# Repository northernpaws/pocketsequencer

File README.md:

# Pocket Sequencer

> This sequencer is being revised in revision 2 as a target for my embedded Rust audio processing framework, Rythm. Revision 2 will be a carrier board for one of the Rythm modules, and use the Rythm engine for the audio and sequencing.
>
> [https://github.com/northernpaws/rythm](https://github.com/northernpaws/rythm)

|  |  |
|:---:|:---:|

[Board Schematic](https://kicanvas.org/?github=https%3A%2F%2Fgithub.com%2Fnorthernpaws%2Fpocketsequencer%2Fblob%2Fmain%2Fhardware%2Fboards%2Fv0.1%2Fpocket_synth.kicad_pro)

[Board v0.1 Errata](hardware/boards/v0.1/README.md)

This repository contains my project for an STM32H7-based sequencer, synthesizer, and sampler, all in a small phone-sized pocketable form factor. 

  * 480 MHz Arm® Cortex®-M7 32-bit Processor (`STM32H743ZIT6`)
    * Floating-point unit
    * DSP instructions
    * High-speed memory controller
    * Quad SPI interface for flash
    * High-speed USB host and device mode
    * Several SAI audio blocks
  * 2.8" 240x320 TFT IPS Display (`ER-TFT028A2-4`)
  * 24 bit Audio Codec (`NAU88C22YG`)
    * DAC: 94dB SNR
    * ADC: 90dB SNR
    * 1W 8Ω BTL speaker driver
    * 40mW 16Ω headphone driver
  * Optional Bluetooth and Wifi (`nRF5430`)
    * Wirelessly connect Bluethooth headphones and speakers
    * Supports various high-fedality audio protocols
    * BLE MIDI
    * Wifi sample management and transfer
  * Interal stereo 8W speakers speaker
  * Internal MEMs microphone
  * SDRAM for sample pool and audio processing
    * Part allocated to in-memory sample pool for project
    * Part allocated to audio effects processing
    * Variable sizes in similar footprint available, up to 512Mbit:
        * 16bit * 48000Hz = 768,000b/s = 0.768Mb/s
        * 128Mb / 0.768Mb/s = 166.66 seconds of mono audio (`IS42S16800J-7TL`)
        * 256Mb / 0.768Mb/s = 333.33 seconds of mono audio (`IS42S16160J-7TLI`)
        * 512Mb / 0.768Mb/s = 666.66 seconds of mono audio (`IS42S16320F-7TLI`)
  * Micro SD Card
    * Saving and loading projects
      * Transfer and back up projects to a computer
    * Saving and loading samples
      * Load samples from a computer
      * Save samples recorded on the device
  * 3.3v NOR Flash (`MT25QUxxxxxx1xW7` 256M/128M/64M)
    * Stores device settings
    * Small storage space for projects and samples without SD card
    * Provides storage for cross-SD card samples
  * USB-C
    * USB-PD fast charging
    * Possible future audio interface mode
    * USB MIDI in and out
  * MIDI in/out via TRS minijack type A
  * 16 Multi-Purpose primary keys
    * Hot-swappable Kalih V1 Choc keyswitches
    * Addressable RGB LEDs for state indicators
  * Accelerometer and Gyroscope (`LSM6DS3`)
    * Can be used as sequencer parameters
    * Can be recorded for automation inputs

## Step Sequencer

The step sequencer on the device is modeled after popular semantics used by hardware sequencers, such as the Elektron Digitone and Digitakt, OP-1, OP-Z, Pocket Operators, Woovebox, etc.

> The hard requirements of the step sequencer and audio engine are not defined yet because they are under active development.

  * As many projects as the SD card or internal memory can store
    * 128 Patterns (TBD)
      * 8-16 Audio or MIDI tracks per pattern (TBD)
    * 8-24 Songs (arrangements of patterns) (TBD)
  * 8-16 voice polyphony (TBD)
    * 2-3 LFO per voice (TBD)

## Audio Samples

The primary audio engine runs in 32-bit and supports stereo audio.

### Sampling

The sampling engine runs 16bit 44.1Khz and saves and loads samples in single-channel mono.

Samples recoded from the internal or external mic are sampled at 24 bits into the device's SDRAM to provide a decent noise floor, and then filtered and downsampled to 16 bits for saving after they've been edited by the user.

The 16bit @ 44.1Khz sampling parameters provdes a good balance between audio quality, and reasonable utilization of the SDRAM without needing extremely large and expensive SDRAM chips:

```
16bit * 48000Hz = 768,000b/s = 0.768Mb/s
128Mb / 0.768Mb/s = 166.66 seconds of mono audio
256Mb / 0.768Mb/s = 333.33 seconds of mono audio
512Mb / 0.768Mb/s = 666.66 seconds of mono audio
```

> Note that some of the space calculated above (actual amount will be configurable) is allocated to the audio effects processing chain, i.e. for reverb and delay. 

## References

### Debugging

 - HardFault: Under XPERIPHERALS in Cortex-debug check the `CFSR_UFSR_BFSR_MMFSR` register to see the fault code and reference: https://community.st.com/t5/stm32-mcus/how-to-debug-a-hardfault-on-an-arm-cortex-m-stm32/ta-p/672235#toc-hId--1471762501

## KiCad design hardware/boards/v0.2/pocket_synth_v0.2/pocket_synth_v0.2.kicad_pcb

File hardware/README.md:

# Hardware

## Components

  * [480 MHz Arm® Cortex®-M7 32-bit Processor (`STM32H743ZIT6`)](https://www.st.com/en/microcontrollers-microprocessors/stm32h743zi.html)
    * Floating-point unit
    * DSP instructions
    * High-speed memory controller
    * Quad SPI interface for flash
    * High-speed USB host and device mode
    * Several SAI audio blocks
  * [24 bit Audio Codec (`NAU88C22YG`)](https://www.nuvoton.com/products/smart-home-audio/audio-converters/audio-codec-series/nau88c22yg/)
    * DAC: 94dB SNR and -84dB THD (“A” weighted)
    * ADC: 90dB SNR and -80dB THD (“A” weighted)
    * Integrated BTL speaker driver: 1W into 8Ω
    * Integrated head-phone driver: 40mW into 16Ω
  * [Optional Bluetooth Audio & MIDI (`nRF5340`)](https://www.nordicsemi.com/Products/nRF5340)
    * Wirelessly connect Bluethooth headphones and speakers
    * Connect devices for BLE MIDI inputs and outputs
    * uFL connector for case-mounted antenna
  * [Optional Wi-Fi (`ESP32-S2-MINI-2U`)](https://www.espressif.com/sites/default/files/documentation/esp32-s2-mini-2_esp32-s2-mini-2u_datasheet_en.pdf)
    * Wi-Fi sample management and transfer
    * uFL connector for case-mounted antenna

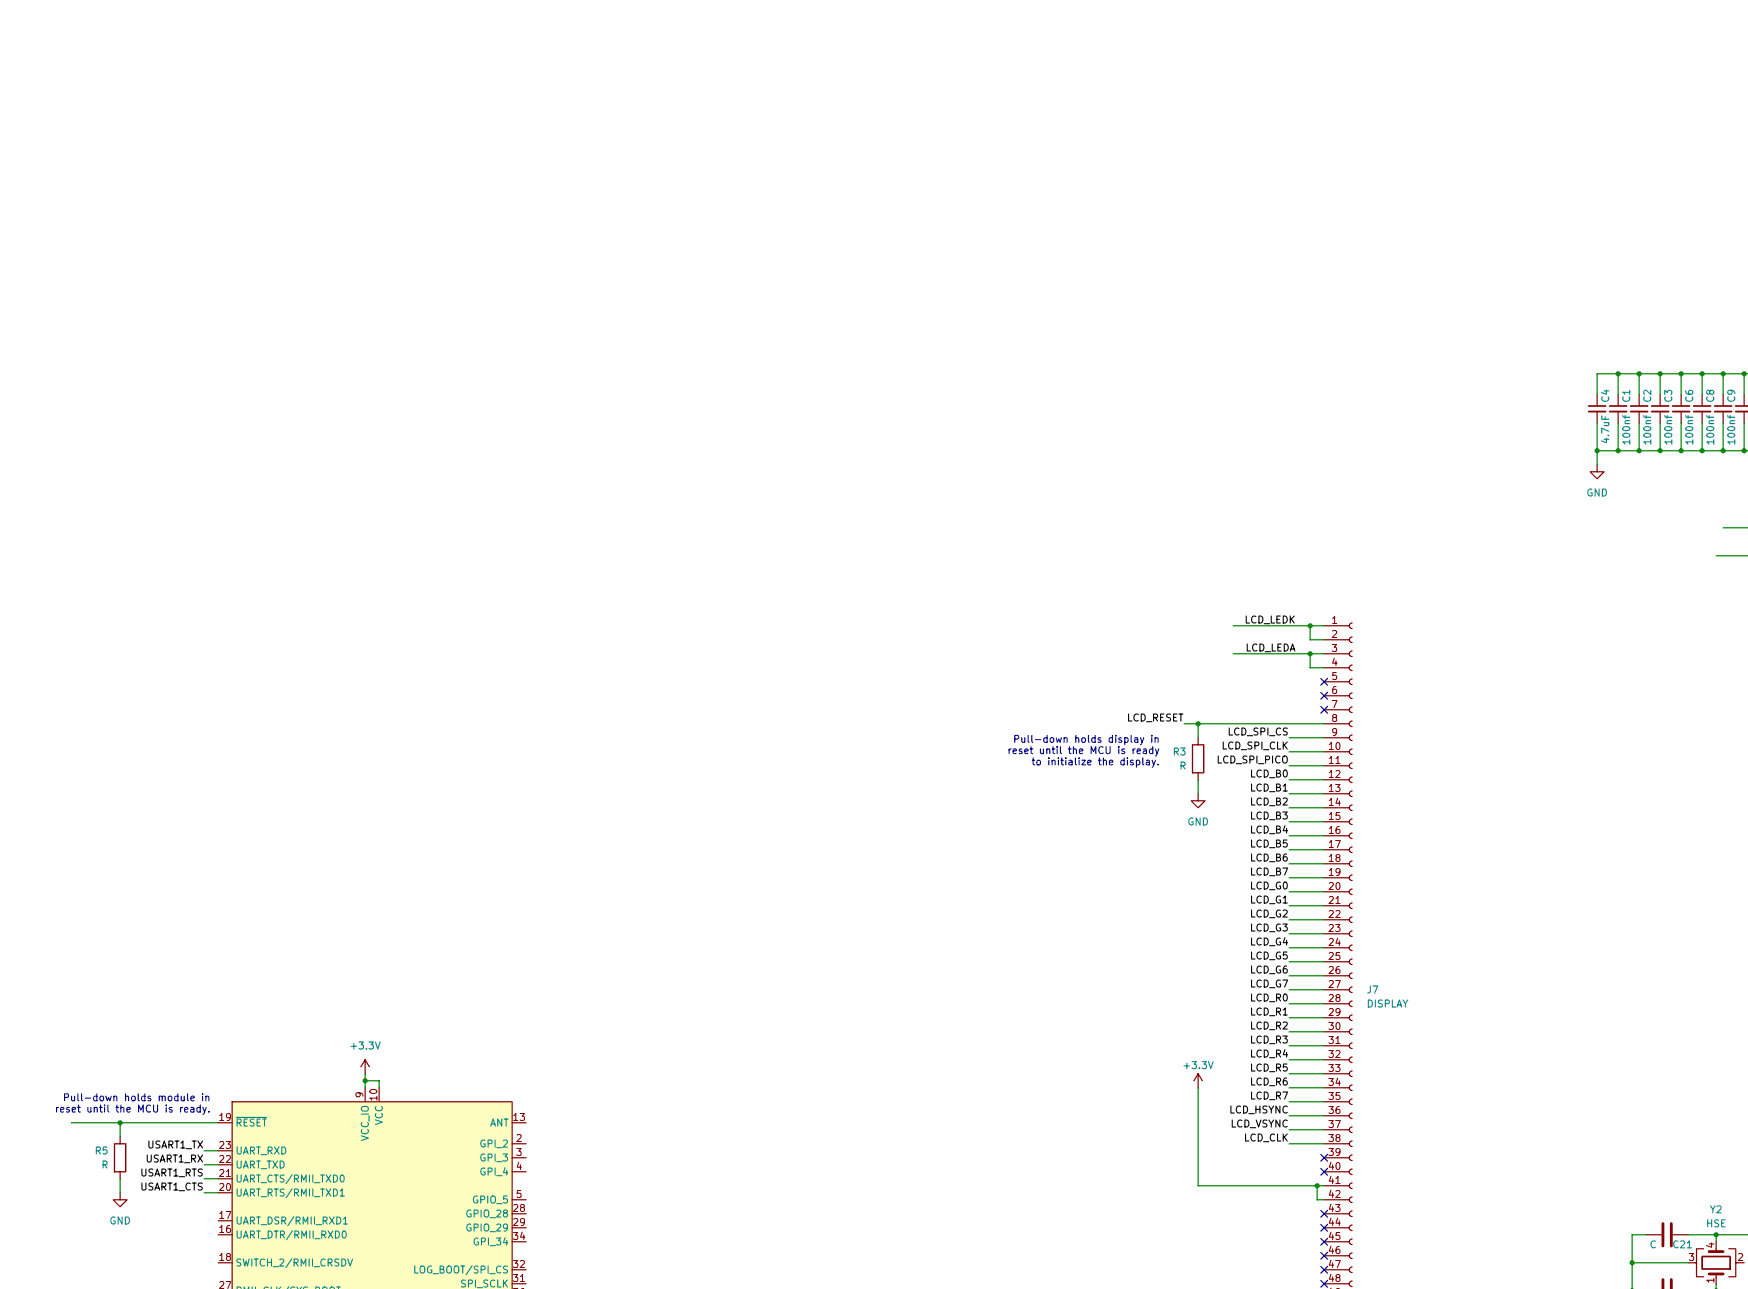
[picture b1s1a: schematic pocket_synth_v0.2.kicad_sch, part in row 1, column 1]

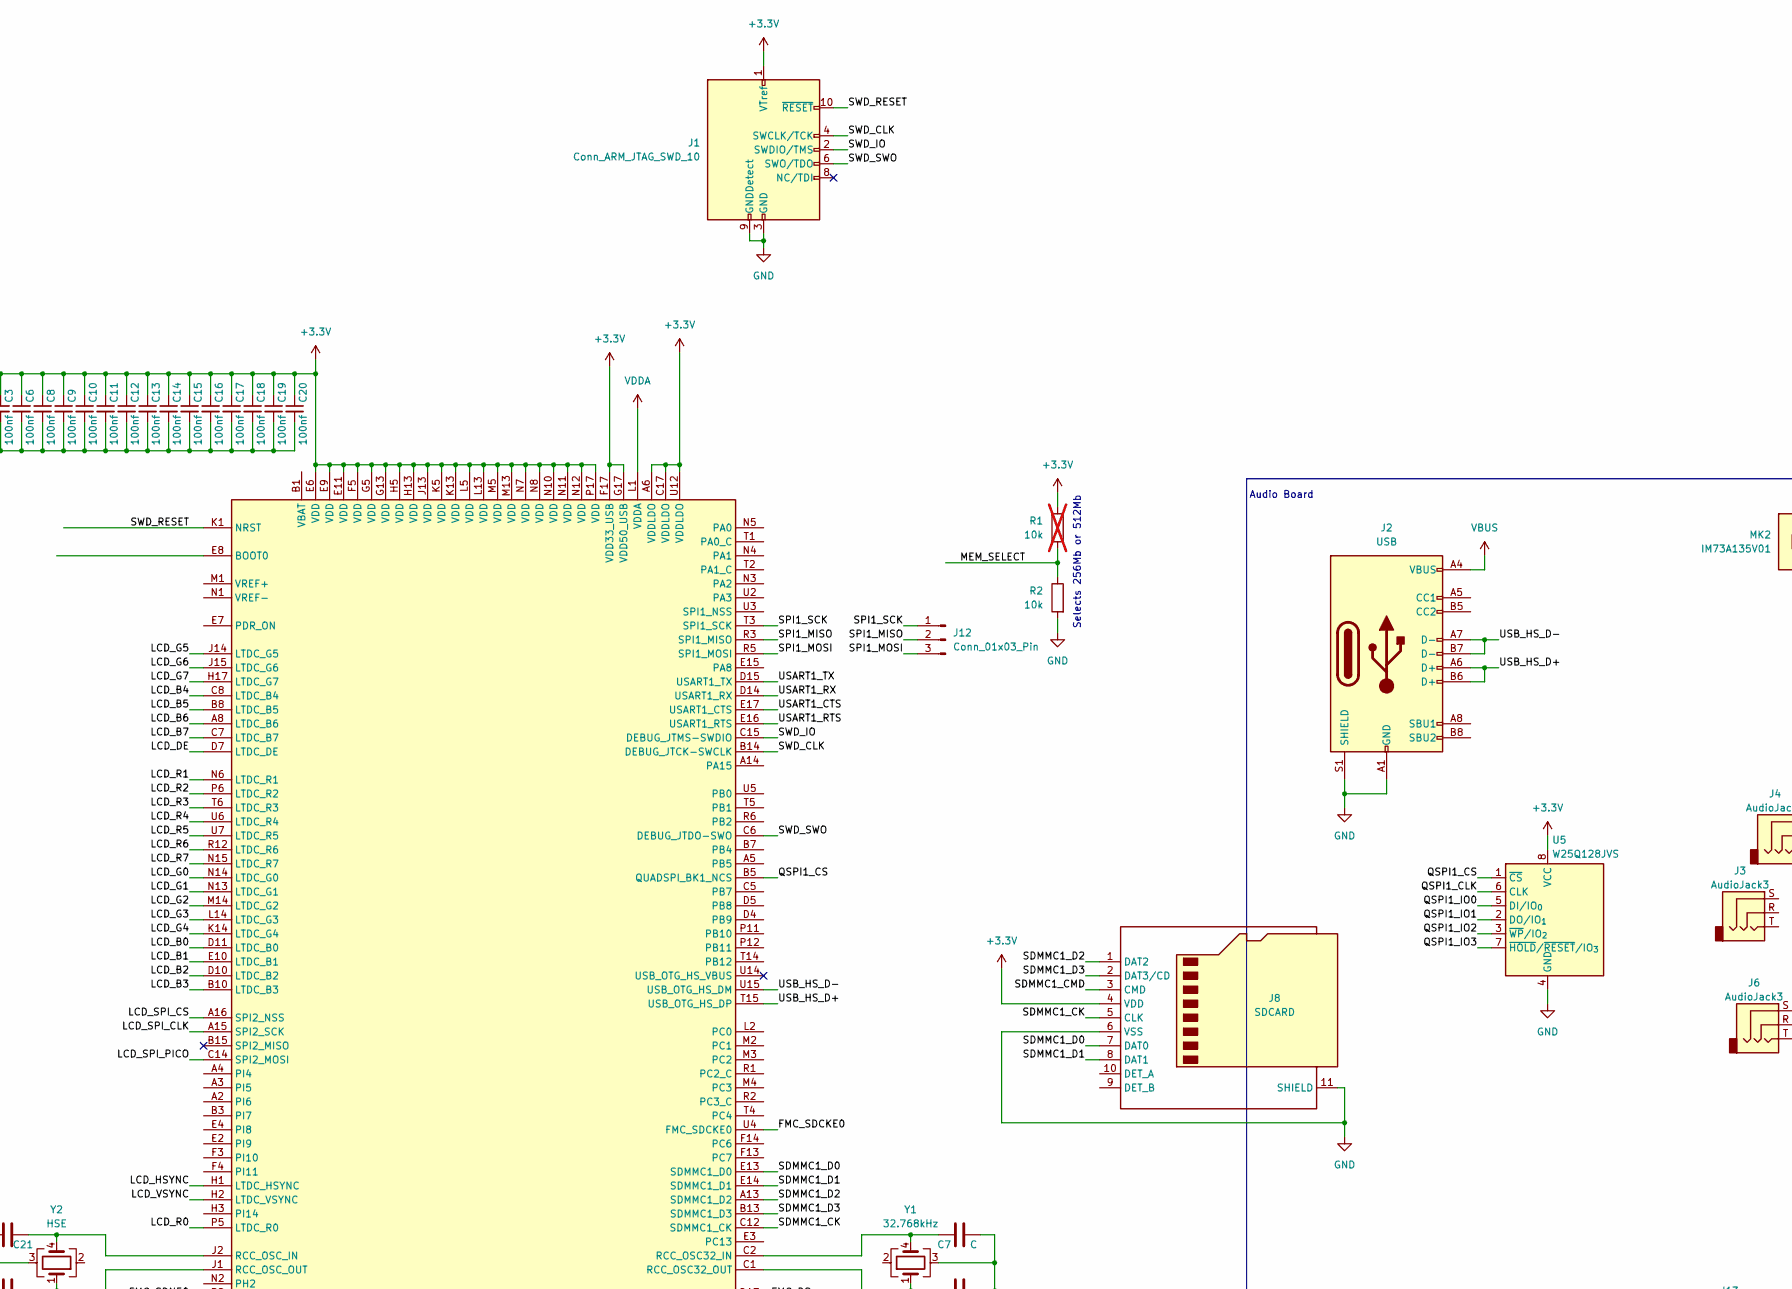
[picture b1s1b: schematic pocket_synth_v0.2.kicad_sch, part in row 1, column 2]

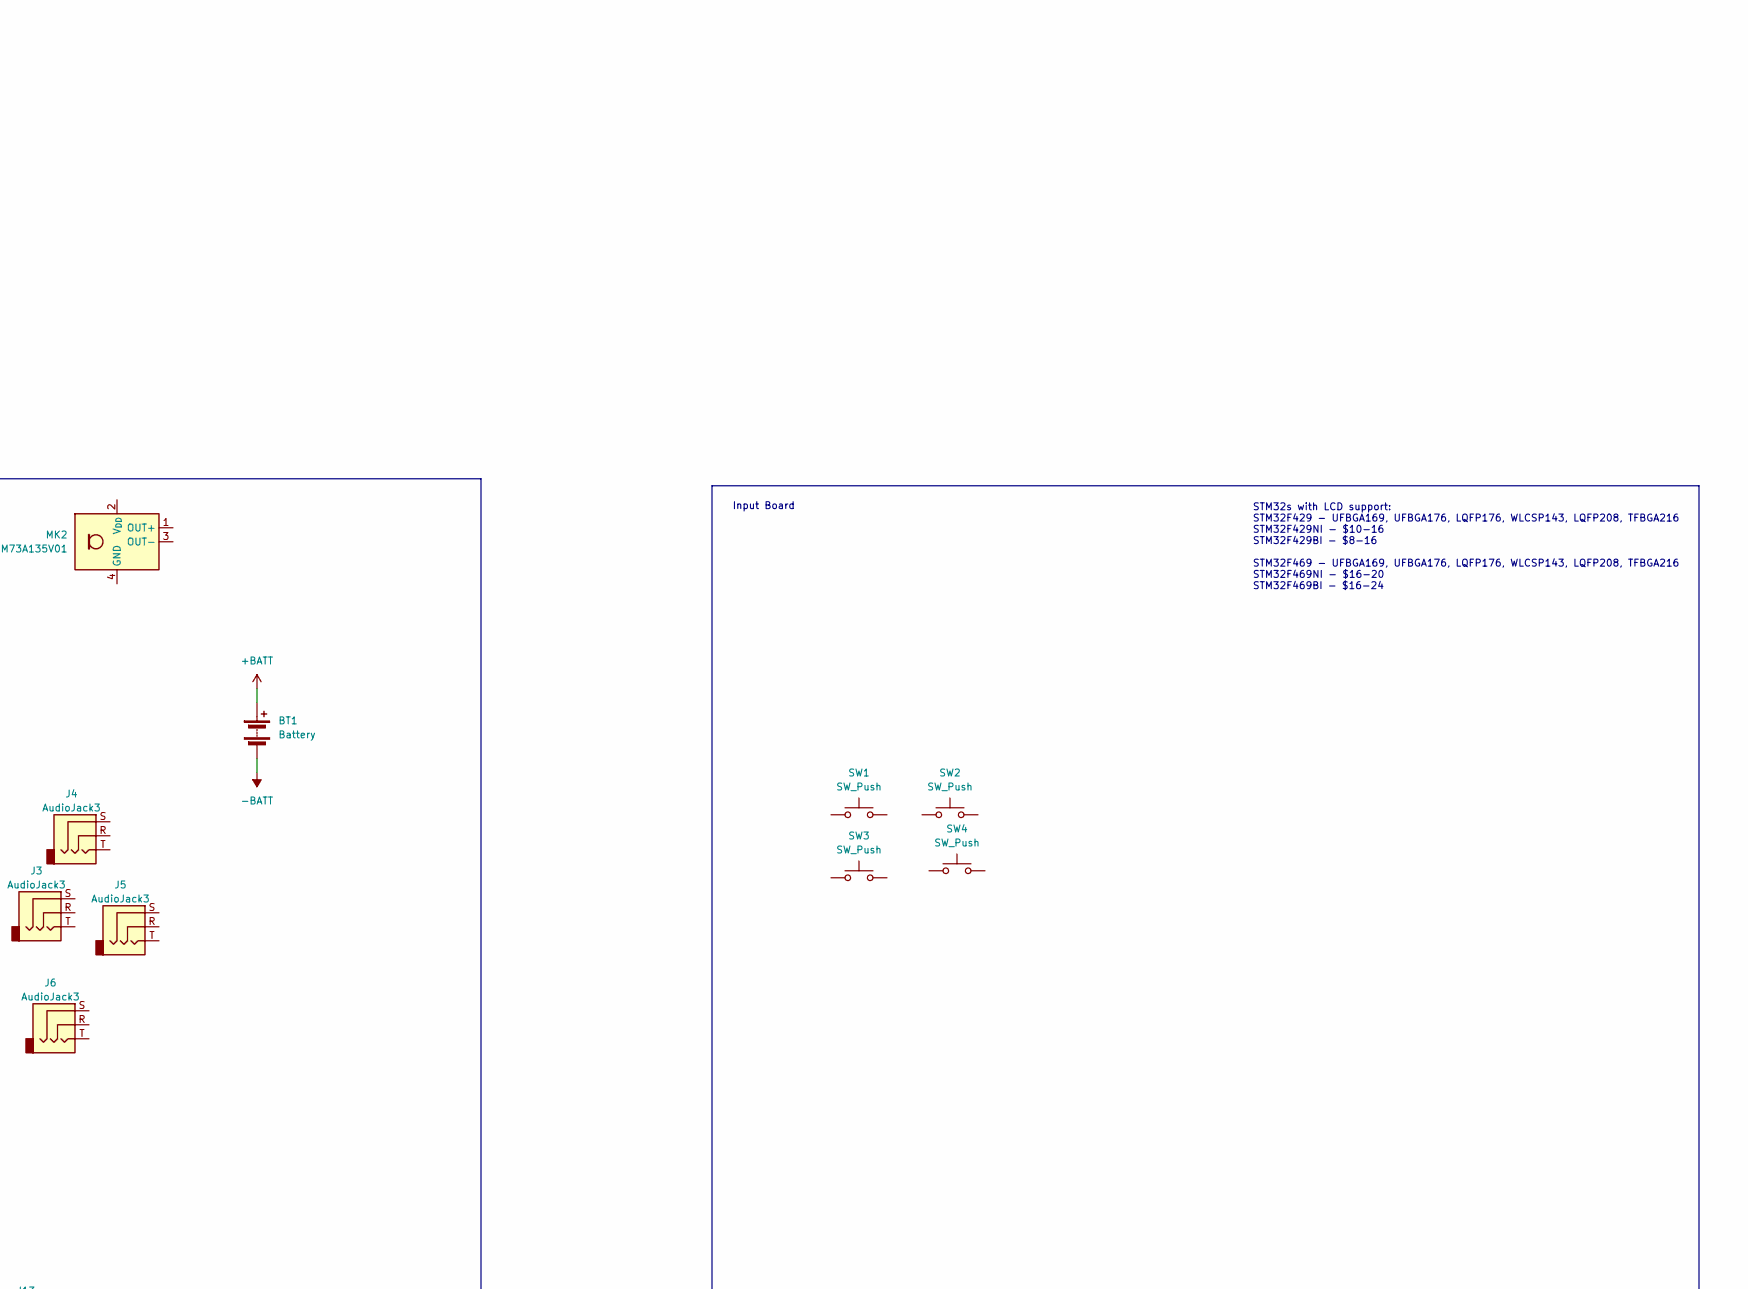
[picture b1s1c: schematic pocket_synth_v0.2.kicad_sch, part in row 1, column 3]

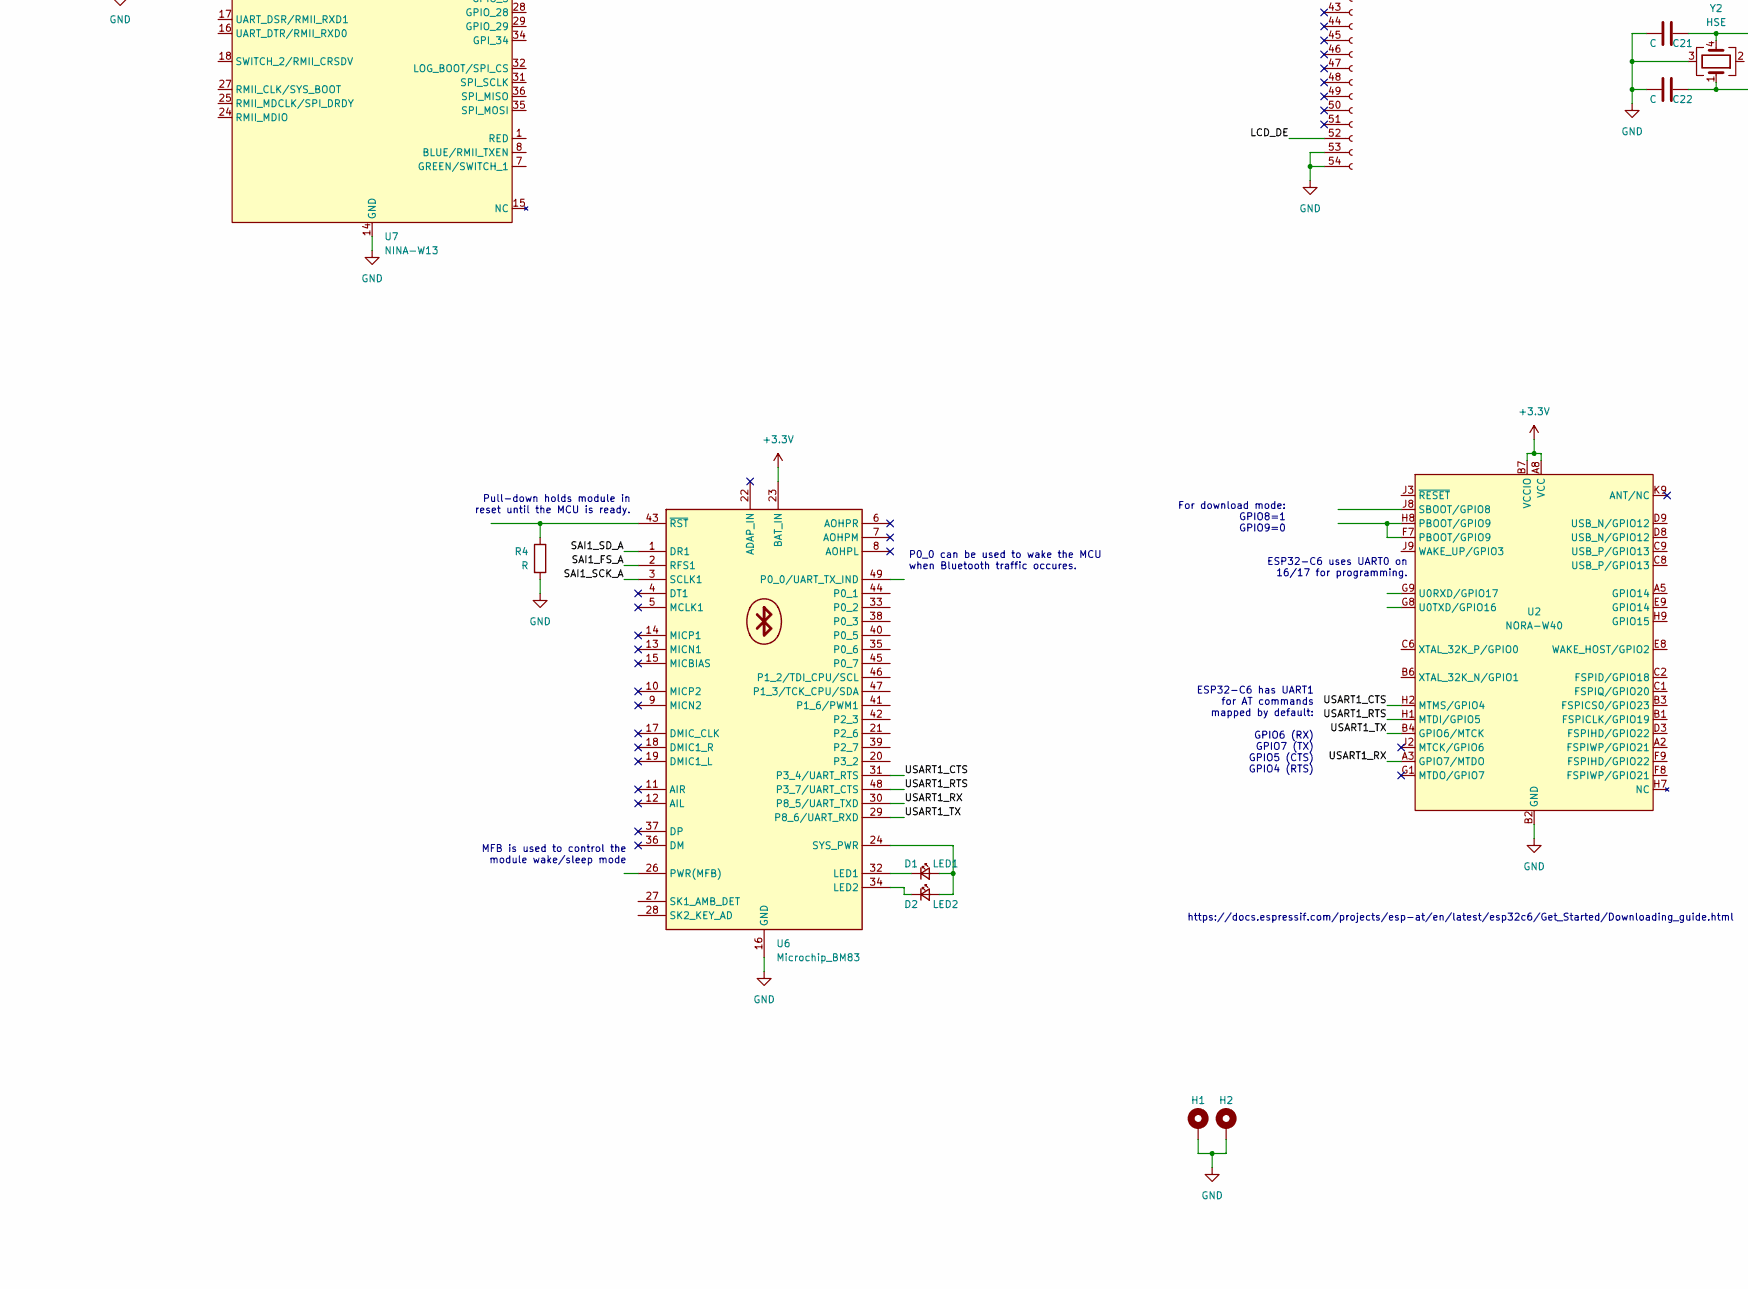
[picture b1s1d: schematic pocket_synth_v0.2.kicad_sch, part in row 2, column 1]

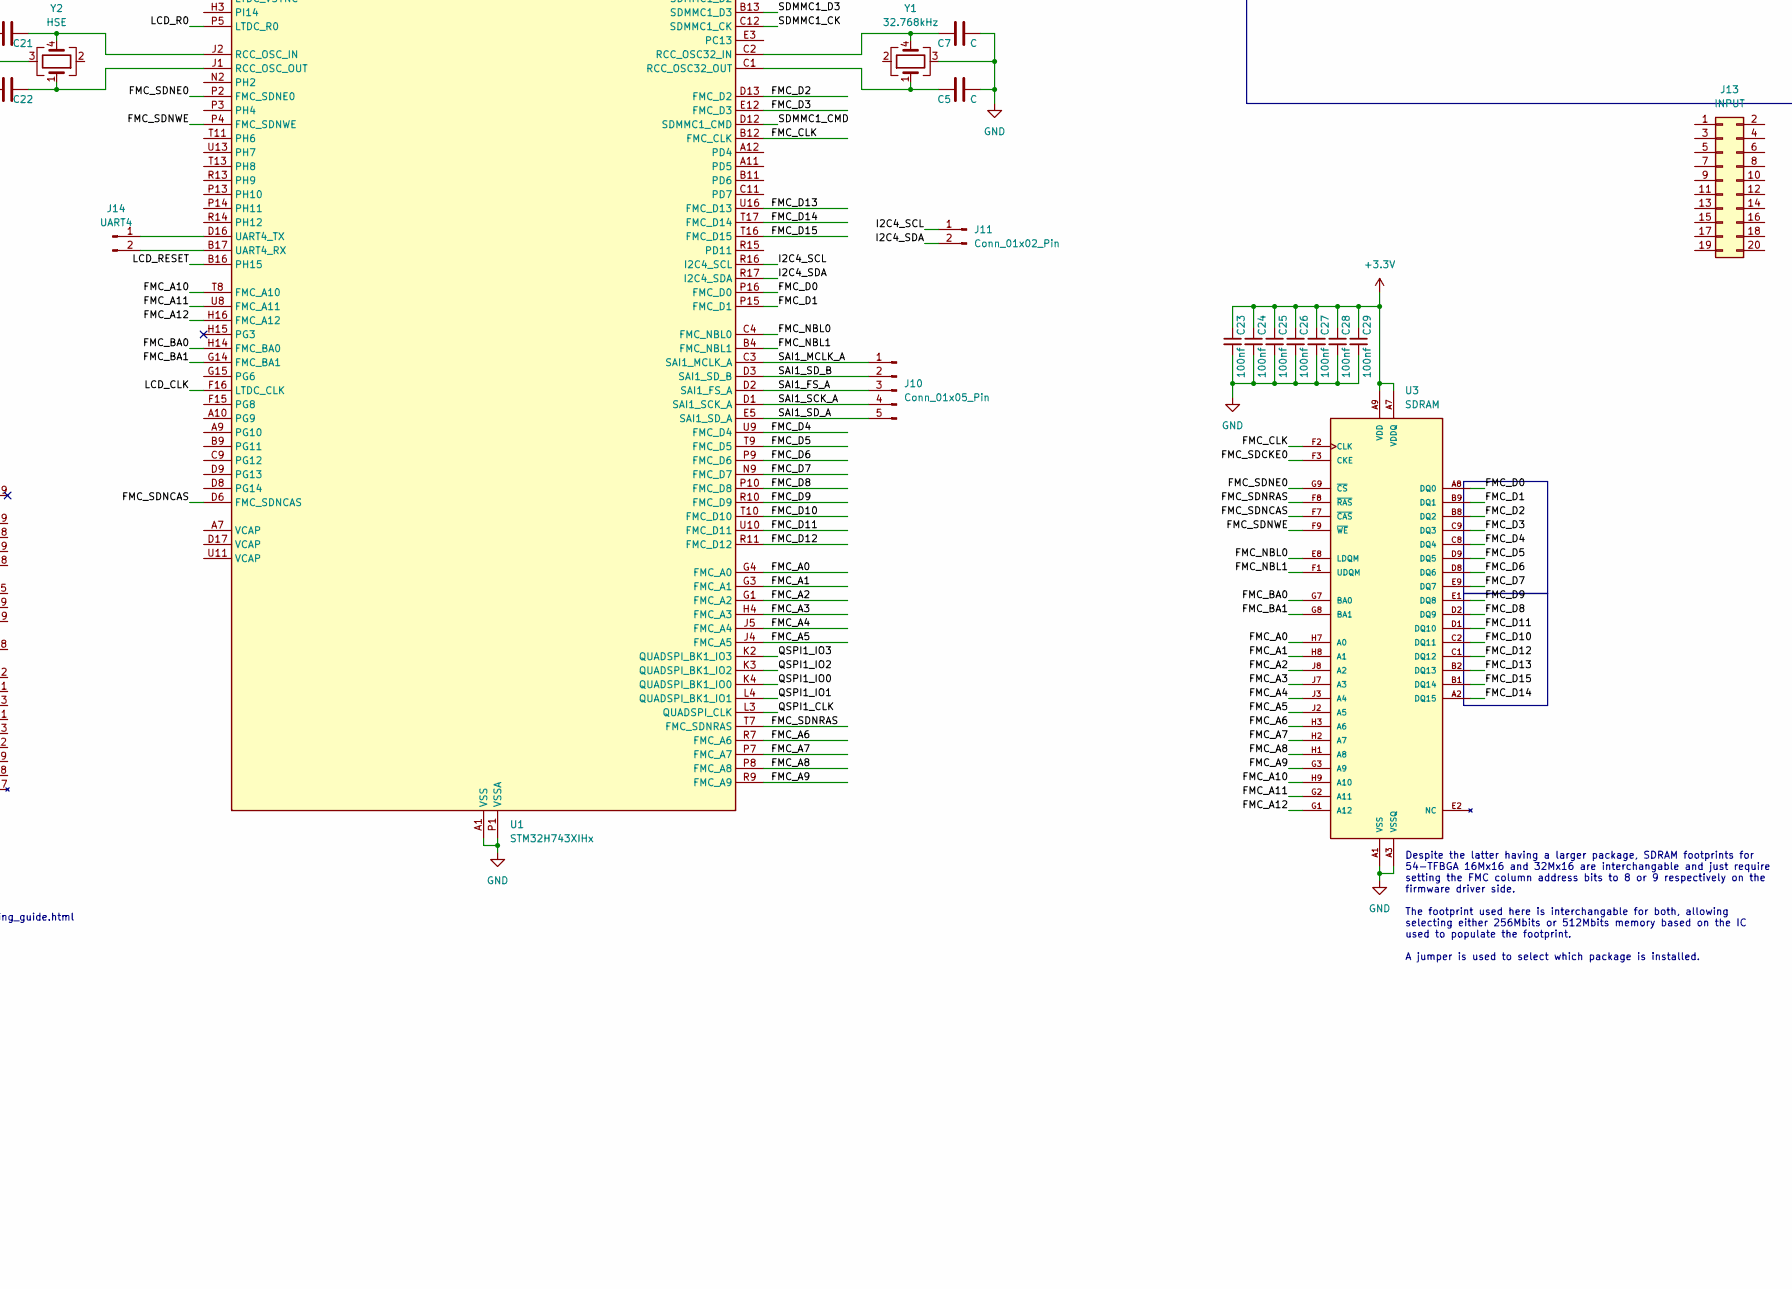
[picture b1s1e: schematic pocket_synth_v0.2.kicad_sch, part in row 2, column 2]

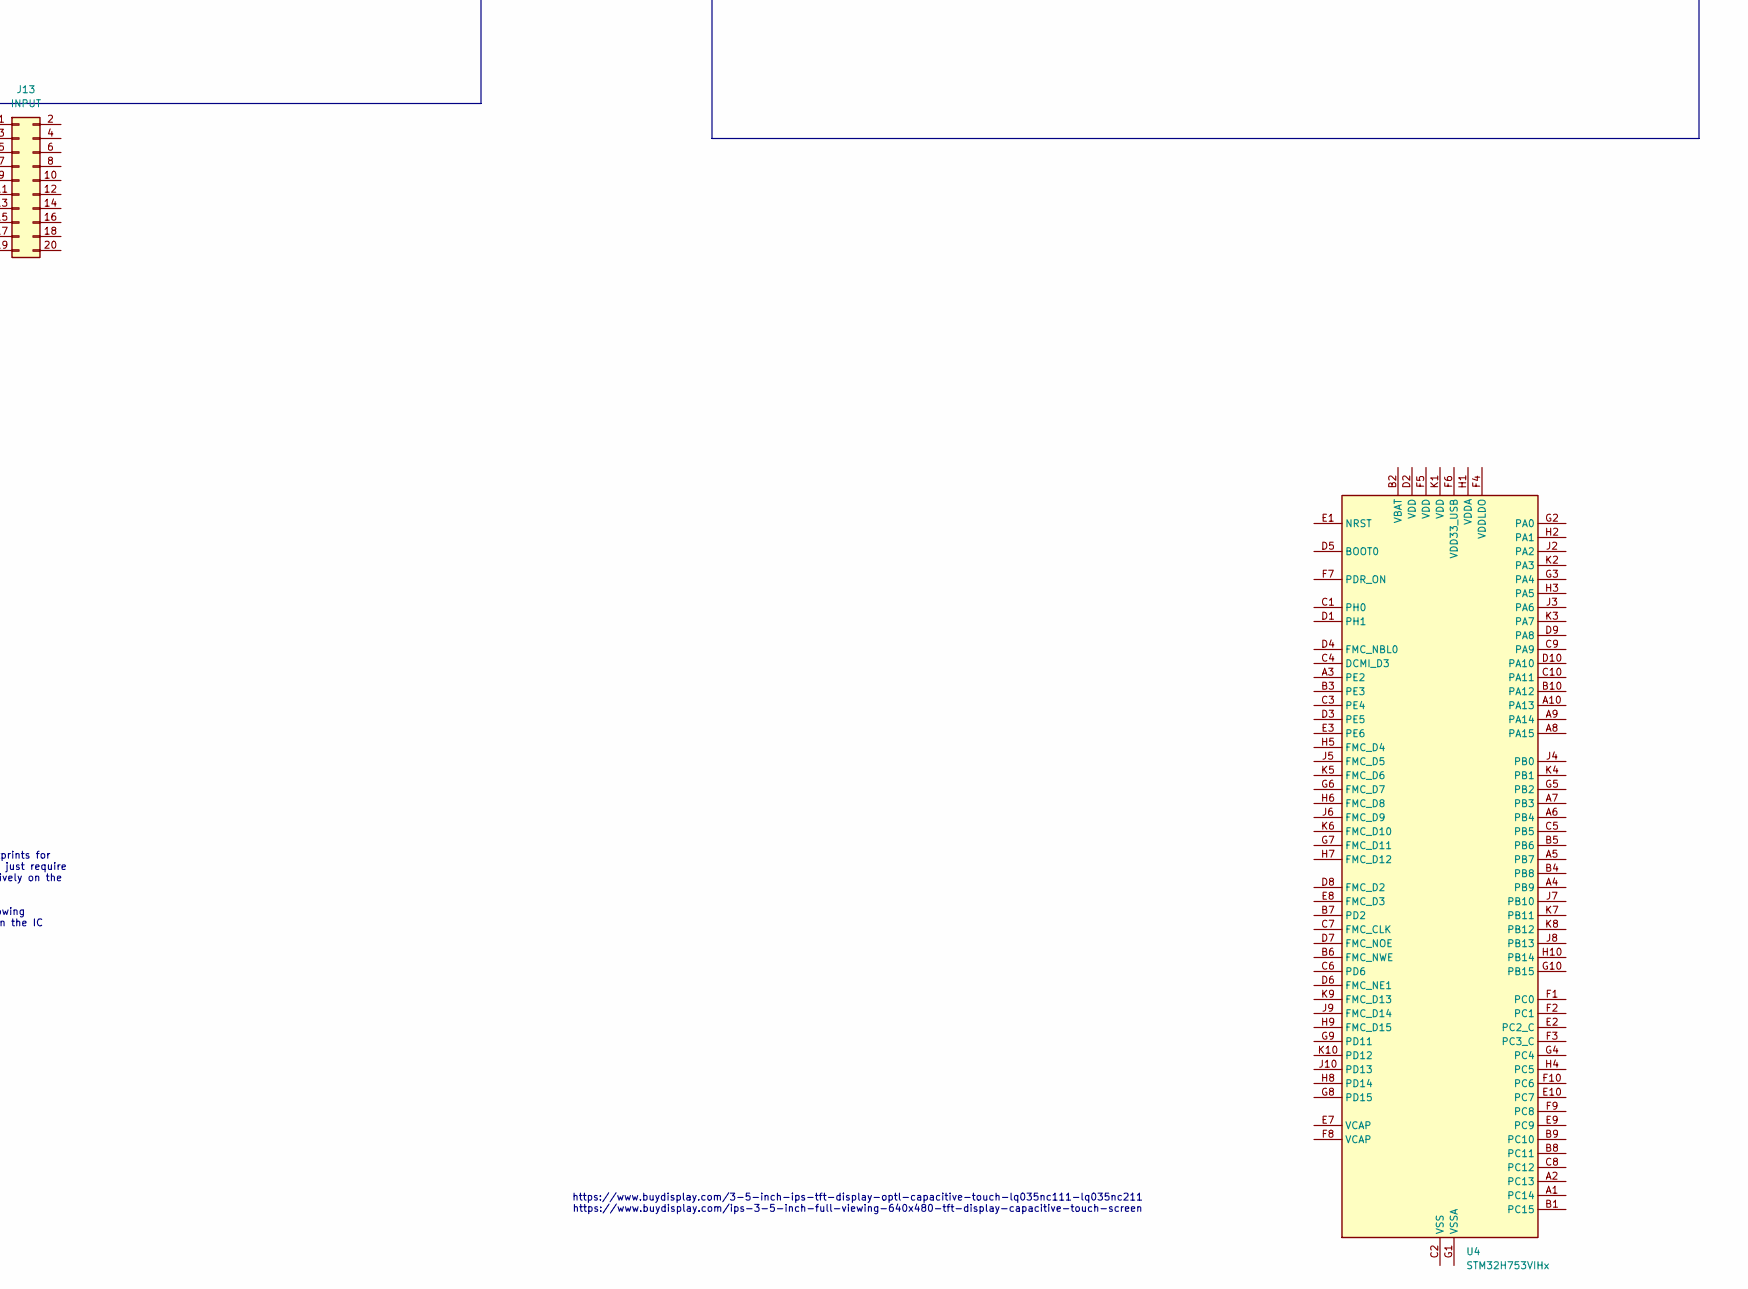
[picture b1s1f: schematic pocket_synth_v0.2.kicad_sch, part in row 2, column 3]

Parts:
BT1: Battery; JST_PH_S2B-PH-K_1x02_P2.00mm_Horizontal
C1, C2, C3, C6, C8, C9, C10, C11, C12, C13, C14, C15, C16, C17, C18, C19, C20, C23, C24, C25, C26, C27, C28, C29: 100nf; C_0402_1005Metric
C4: 4.7uF; C_0402_1005Metric
C5, C7, C21, C22: C; C_0805_2012Metric
D1: LED1
D2: LED2
H1, H2: MountingHole_Pad; MountingHole_2.2mm_M2_Pad
J1: Conn_ARM_JTAG_SWD_10; PinHeader_2x05_P1.27mm_Vertical_SMD
J2: USB; USB_C_Receptacle_HCTL_HC-TYPE-C-16P-01A
J3, J4, J5, J6: AudioJack3; Jack_3.5mm_CUI_SJ-3523-SMT_Horizontal
J7: DISPLAY; Amphenol_F32Q-1A7x1-11054_1x54-1MP_P0.5mm_Horizontal
J8: SDCARD; microSD_HC_Hirose_DM3AT-SF-PEJM5
J10: Conn_01x05_Pin; PinHeader_1x05_P1.00mm_Vertical
J11: Conn_01x02_Pin; PinHeader_1x02_P1.00mm_Vertical
J12: Conn_01x03_Pin; PinHeader_1x03_P1.00mm_Vertical
J13: INPUT; Hirose_DF40C-20DS-0.4V_2x10_P0.4mm
J14: UART4; PinHeader_1x02_P1.00mm_Vertical
MK2: IM73A135V01; Infineon_PG-LLGA-5-2
R1: 10k; R_0603_1608Metric_Pad0.98x0.95mm_HandSolder; not fitted
R2: 10k; R_0603_1608Metric_Pad0.98x0.95mm_HandSolder
R3, R4, R5: R; R_0603_1608Metric
SW1, SW2, SW3, SW4: SW_Push; SW_SPST_SKQG_WithoutStem
U1: STM32H743XIHx; TFBGA-265_14x14mm_Layout17x17_P0.8mm
U2: NORA-W40
U3: SDRAM; IC54_IS42S16320F-7BLI_ISI; PARTREV Rev. 1.2; DigiKey_Part_Number 1450-AS4C32M16SB-7BIN-ND
U4: STM32H753VIHx; TFBGA-100_8x8mm_Layout10x10_P0.8mm
U5: W25Q128JVS; SOIC-8_5.3x5.3mm_P1.27mm
U6: Microchip_BM83
U7: NINA-W13; ublox-NINA-W13
Y1: 32.768kHz; Crystal_SMD_Abracon_ABM10-4Pin_2.5x2.0mm
Y2: HSE; Crystal_SMD_Abracon_ABM10-4Pin_2.5x2.0mm

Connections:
+3.3V: C1.1, C2.1, C3.1, C4.1, C6.1, C8.1, C9.1, C10.1, C11.1, C12.1, C13.1, C14.1, C15.1, C16.1, C17.1, C18.1, C19.1, C20.1, C23.1, C24.1, C25.1, C26.1, C27.1, C28.1, C29.1, J1.1 (VTref), J7.41, J7.42, J8.4 (VDD), R1.1, U1.A6 (VDDLDO), U1.C17 (VDDLDO), U1.E6 (VDD), U1.E9 (VDD), U1.E11 (VDD), U1.F5 (VDD), U1.F17 (VDD33_USB), U1.G5 (VDD), U1.G13 (VDD), U1.G17 (VDD50_USB), U1.H5 (VDD), U1.H13 (VDD), U1.J13 (VDD), U1.K5 (VDD), U1.K13 (VDD), U1.L5 (VDD), U1.L13 (VDD), U1.M5 (VDD), U1.M13 (VDD), U1.N7 (VDD), U1.N8 (VDD), U1.N10 (VDD), U1.N11 (VDD), U1.N12 (VDD), U1.P17 (VDD), U1.U12 (VDDLDO), U2.A7 (VCCIO), U2.A8 (VCC), U2.B7 (VCCIO), U3.A7 (VDDQ), U3.A9 (VDD), U3.B3 (VDDQ), U3.C7 (VDDQ), U3.D3 (VDDQ), U3.E7 (VDD), U3.J9 (VDD), U5.8 (VCC), U6.23 (BAT_IN), U7.9 (VCC_IO), U7.10 (VCC)
+BATT: BT1.1 (+)
-BATT: BT1.2 (-)
/FMC_A0: U1.G4 (FMC_A0), U3.H7 (A0)
/FMC_A1: U1.G3 (FMC_A1), U3.H8 (A1)
/FMC_A2: U1.G1 (FMC_A2), U3.J8 (A2)
/FMC_A3: U1.H4 (FMC_A3), U3.J7 (A3)
/FMC_A4: U1.J5 (FMC_A4), U3.J3 (A4)
/FMC_A5: U1.J4 (FMC_A5), U3.J2 (A5)
/FMC_A6: U1.R7 (FMC_A6), U3.H3 (A6)
/FMC_A7: U1.P7 (FMC_A7), U3.H2 (A7)
/FMC_A8: U1.P8 (FMC_A8), U3.H1 (A8)
/FMC_A9: U1.R9 (FMC_A9), U3.G3 (A9)
/FMC_A10: U1.T8 (FMC_A10), U3.H9 (A10)
/FMC_A11: U1.U8 (FMC_A11), U3.G2 (A11)
/FMC_A12: U1.H16 (FMC_A12), U3.G1 (A12)
/FMC_BA0: U1.H14 (FMC_BA0), U3.G7 (BA0)
/FMC_BA1: U1.G14 (FMC_BA1), U3.G8 (BA1)
/FMC_CLK: U1.B12 (FMC_CLK), U3.F2 (CLK)
/FMC_D0: U1.P16 (FMC_D0), U3.A8 (DQ0)
/FMC_D1: U1.P15 (FMC_D1), U3.B9 (DQ1)
/FMC_D2: U1.D13 (FMC_D2), U3.B8 (DQ2)
/FMC_D3: U1.E12 (FMC_D3), U3.C9 (DQ3)
/FMC_D4: U1.U9 (FMC_D4), U3.C8 (DQ4)
/FMC_D5: U1.T9 (FMC_D5), U3.D9 (DQ5)
/FMC_D6: U1.P9 (FMC_D6), U3.D8 (DQ6)
/FMC_D7: U1.N9 (FMC_D7), U3.E9 (DQ7)
/FMC_D8: U1.P10 (FMC_D8), U3.D2 (DQ9)
/FMC_D9: U1.R10 (FMC_D9), U3.E1 (DQ8)
/FMC_D10: U1.T10 (FMC_D10), U3.C2 (DQ11)
/FMC_D11: U1.U10 (FMC_D11), U3.D1 (DQ10)
/FMC_D12: U1.R11 (FMC_D12), U3.C1 (DQ12)
/FMC_D13: U1.U16 (FMC_D13), U3.B2 (DQ13)
/FMC_D14: U1.T17 (FMC_D14), U3.A2 (DQ15)
/FMC_D15: U1.T16 (FMC_D15), U3.B1 (DQ14)
/FMC_NBL0: U1.C4 (FMC_NBL0), U3.E8 (LDQM)
/FMC_NBL1: U1.B4 (FMC_NBL1), U3.F1 (UDQM)
/FMC_SDCKE0: U1.U4 (FMC_SDCKE0), U3.F3 (CKE)
/FMC_SDNCAS: U1.D6 (FMC_SDNCAS), U3.F7 (~CAS)
/FMC_SDNE0: U1.P2 (FMC_SDNE0), U3.G9 (~CS)
/FMC_SDNRAS: U1.T7 (FMC_SDNRAS), U3.F8 (~RAS)
/FMC_SDNWE: U1.P4 (FMC_SDNWE), U3.F9 (~WE)
/I2C4_SCL: J11.1, U1.R16 (I2C4_SCL)
/I2C4_SDA: J11.2, U1.R17 (I2C4_SDA)
/LCD_B0: J7.12, U1.D11 (LTDC_B0)
/LCD_B1: J7.13, U1.E10 (LTDC_B1)
/LCD_B2: J7.14, U1.D10 (LTDC_B2)
/LCD_B3: J7.15, U1.B10 (LTDC_B3)
/LCD_B4: J7.16, U1.C8 (LTDC_B4)
/LCD_B5: J7.17, U1.B8 (LTDC_B5)
/LCD_B6: J7.18, U1.A8 (LTDC_B6)
/LCD_B7: J7.19, U1.C7 (LTDC_B7)
/LCD_CLK: J7.38, U1.F16 (LTDC_CLK)
/LCD_DE: J7.52, U1.D7 (LTDC_DE)
/LCD_G0: J7.20, U1.N14 (LTDC_G0)
/LCD_G1: J7.21, U1.N13 (LTDC_G1)
/LCD_G2: J7.22, U1.M14 (LTDC_G2)
/LCD_G3: J7.23, U1.L14 (LTDC_G3)
/LCD_G4: J7.24, U1.K14 (LTDC_G4)
/LCD_G5: J7.25, U1.J14 (LTDC_G5)
/LCD_G6: J7.26, U1.J15 (LTDC_G6)
/LCD_G7: J7.27, U1.H17 (LTDC_G7)
/LCD_HSYNC: J7.36, U1.H1 (LTDC_HSYNC)
/LCD_LEDA: J7.3, J7.4
/LCD_LEDK: J7.1, J7.2
/LCD_R0: J7.28, U1.P5 (LTDC_R0)
/LCD_R1: J7.29, U1.N6 (LTDC_R1)
/LCD_R2: J7.30, U1.P6 (LTDC_R2)
/LCD_R3: J7.31, U1.T6 (LTDC_R3)
/LCD_R4: J7.32, U1.U6 (LTDC_R4)
/LCD_R5: J7.33, U1.U7 (LTDC_R5)
/LCD_R6: J7.34, U1.R12 (LTDC_R6)
/LCD_R7: J7.35, U1.N15 (LTDC_R7)
/LCD_RESET: J7.8, R3.1, U1.B16 (PH15)
/LCD_SPI_CLK: J7.10, U1.A15 (SPI2_SCK)
/LCD_SPI_CS: J7.9, U1.A16 (SPI2_NSS)
/LCD_SPI_PICO: J7.11, U1.C14 (SPI2_MOSI)
/LCD_VSYNC: J7.37, U1.H2 (LTDC_VSYNC)
/MEM_SELECT: R1.2, R2.1
/QSPI1_CLK: U1.L3 (QUADSPI_CLK), U5.6 (CLK)
/QSPI1_CS: U1.B5 (QUADSPI_BK1_NCS), U5.1 (~CS)
/QSPI1_IO0: U1.K4 (QUADSPI_BK1_IO0), U5.5 (DI/IO_{0})
/QSPI1_IO1: U1.L4 (QUADSPI_BK1_IO1), U5.2 (DO/IO_{1})
/QSPI1_IO2: U1.K3 (QUADSPI_BK1_IO2), U5.3 (~WP/IO_{2})
/QSPI1_IO3: U1.K2 (QUADSPI_BK1_IO3), U5.7 (~HOLD/~RESET/IO_{3})
/SAI1_FS_A: J10.3, U1.D2 (SAI1_FS_A), U6.2 (RFS1)
/SAI1_MCLK_A: J10.1, U1.C3 (SAI1_MCLK_A)
/SAI1_SCK_A: J10.4, U1.D1 (SAI1_SCK_A), U6.3 (SCLK1)
/SAI1_SD_A: J10.5, U1.E5 (SAI1_SD_A), U6.1 (DR1)
/SAI1_SD_B: J10.2, U1.D3 (SAI1_SD_B)
/SDMMC1_CK: J8.5 (CLK), U1.C12 (SDMMC1_CK)
/SDMMC1_CMD: J8.3 (CMD), U1.D12 (SDMMC1_CMD)
/SDMMC1_D0: J8.7 (DAT0), U1.E13 (SDMMC1_D0)
/SDMMC1_D1: J8.8 (DAT1), U1.E14 (SDMMC1_D1)
/SDMMC1_D2: J8.1 (DAT2), U1.A13 (SDMMC1_D2)
/SDMMC1_D3: J8.2 (DAT3/CD), U1.B13 (SDMMC1_D3)
/SPI1_MISO: J12.2, U1.R3 (SPI1_MISO)
/SPI1_MOSI: J12.3, U1.R5 (SPI1_MOSI)
/SPI1_SCK: J12.1, U1.T3 (SPI1_SCK)
/SWD_CLK: J1.4 (SWCLK/TCK), U1.B14 (DEBUG_JTCK-SWCLK)
/SWD_IO: J1.2 (SWDIO/TMS), U1.C15 (DEBUG_JTMS-SWDIO)
/SWD_RESET: J1.10 (~RESET), U1.K1 (NRST)
/SWD_SWO: J1.6 (SWO/TDO), U1.C6 (DEBUG_JTDO-SWO)
/USART1_CTS: U1.E17 (USART1_CTS), U2.H2 (MTMS/GPIO4), U6.31 (P3_4/UART_RTS), U7.20 (UART_RTS/RMII_TXD1)
/USART1_RTS: U1.E16 (USART1_RTS), U2.H1 (MTDI/GPIO5), U6.48 (P3_7/UART_CTS), U7.21 (UART_CTS/RMII_TXD0)
/USART1_RX: U1.D14 (USART1_RX), U2.A3 (GPIO7/MTDO), U6.30 (P8_5/UART_TXD), U7.22 (UART_TXD)
/USART1_TX: U1.D15 (USART1_TX), U2.B4 (GPIO6/MTCK), U6.29 (P8_6/UART_RXD), U7.23 (UART_RXD)
/USB_HS_D+: J2.A6 (D+), J2.B6 (D+), U1.T15 (USB_OTG_HS_DP)
/USB_HS_D-: J2.A7 (D-), J2.B7 (D-), U1.U15 (USB_OTG_HS_DM)
GND: C1.2, C2.2, C3.2, C4.2, C5.2, C6.2, C7.2, C8.2, C9.2, C10.2, C11.2, C12.2, C13.2, C14.2, C15.2, C16.2, C17.2, C18.2, C19.2, C20.2, C21.2, C22.2, C23.2, C24.2, C25.2, C26.2, C27.2, C28.2, C29.2, H1.1, H2.1, J1.3 (GND), J1.5 (GND), J1.9 (GNDDetect), J2.A1 (GND), J2.A12 (GND), J2.B1 (GND), J2.B12 (GND), J2.S1 (SHIELD), J7.53, J7.54, J8.6 (VSS), J8.11 (SHIELD), R2.2, R3.2, R4.2, R5.2, U1.A1 (VSS), U1.A17 (VSS), U1.B2 (VSS), U1.B6 (VSS), U1.C10 (VSS), U1.C13 (VSS), U1.C16 (VSS), U1.F1 (VSS), U1.F2 (VSS), U1.G2 (VSS), U1.G7 (VSS), U1.G8 (VSS), U1.G9 (VSS), U1.G10 (VSS), U1.G11 (VSS), U1.G16 (VSS), U1.H7 (VSS), U1.H8 (VSS), U1.H9 (VSS), U1.H10 (VSS), U1.H11 (VSS), U1.J3 (VSS), U1.J7 (VSS), U1.J8 (VSS), U1.J9 (VSS), U1.J10 (VSS), U1.J11 (VSS), U1.J16 (VSS), U1.J17 (VSS), U1.K7 (VSS), U1.K8 (VSS), U1.K9 (VSS), U1.K10 (VSS), U1.K11 (VSS), U1.K15 (VSS), U1.L7 (VSS), U1.L8 (VSS), U1.L9 (VSS), U1.L10 (VSS), U1.L11 (VSS), U1.L15 (VSS), U1.M15 (VSS), U1.N16 (VSS), U1.P1 (VSSA), U1.R4 (VSS), U1.R8 (VSS), U1.T12 (VSS), U1.U1 (VSS), U1.U17 (VSS), U2.A1 (GND), U2.A9 (GND), U2.B2 (GND), U2.B8 (GND), U2.E4 (GND), U2.E5 (GND), U2.F4 (GND), U2.F5 (GND), U2.K2 (GND), U2.K3 (GND), U2.K5 (GND), U2.K7 (GND), U2.K8 (GND), U2.L1 (GND), U2.L9 (GND), U2.M1 (GND), U2.M2 (GND), U2.M8 (GND), U2.M9 (GND), U3.A1 (VSS), U3.A3 (VSSQ), U3.B7 (VSSQ), U3.C3 (VSSQ), U3.D7 (VSSQ), U3.E3 (VSS), U3.J1 (VSS), U5.4 (GND), U6.16 (GND), U6.50 (GND), U6.56 (GND), U6.57 (GND), U7.6 (GND), U7.12 (GND), U7.14 (GND), U7.26 (GND), U7.30 (GND), U7.37 (GND), U7.38 (GND), U7.39 (GND), U7.40 (GND), U7.41 (GND), U7.42 (GND), U7.43 (GND), U7.44 (GND), U7.45 (GND), U7.46 (GND), U7.47 (GND), U7.48 (GND), Y1.3, Y2.3
unnamed: D1.2 (A), D2.2 (A), U6.24 (SYS_PWR)
unnamed: D1.1 (K), U6.32 (LED1)
unnamed: D2.1 (K), U6.34 (LED2)
unnamed: J14.1, U1.D16 (UART4_TX)
unnamed: J14.2, U1.B17 (UART4_RX)
unnamed: MK2.4 (GND), MK2.5 (GND)
unnamed: C7.1, U1.C2 (RCC_OSC32_IN), Y1.4
unnamed: C5.1, U1.C1 (RCC_OSC32_OUT), Y1.1
unnamed: C21.1, U1.J2 (RCC_OSC_IN), Y2.4
unnamed: C22.1, U1.J1 (RCC_OSC_OUT), Y2.1
unnamed: U2.F7 (PBOOT/GPIO9), U2.H8 (PBOOT/GPIO9)
unnamed: U4.C2 (VSS), U4.E4 (VSS), U4.E5 (VSS), U4.E6 (VSS), U4.J1 (VSS)
unnamed: R4.1, U6.43 (~RST)
unnamed: R5.1, U7.19 (~RESET)
VBUS: J2.A4 (VBUS), J2.A9 (VBUS), J2.B4 (VBUS), J2.B9 (VBUS)
VDDA: U1.L1 (VDDA)

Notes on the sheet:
Audio Board
Pull-down holds module in reset until the MCU is ready.
P0_0 can be used to wake the MCU when Bluetooth traffic occures.
MFB is used to control the module wake/sleep mode
STM32s with LCD support: STM32F429 - UFBGA169, UFBGA176, LQFP176, WLCSP143, LQFP208, TFBGA216 STM32F429NI - $10-16 STM32F429BI - $8-16 STM32F469 - UFBGA169, UFBGA176, LQFP176, WLCSP143, LQFP208, TFBGA216 STM32F469NI - $16-20 STM32F469BI - $16-24
ESP32-C6 has UART1 for AT commands mapped by default: GPIO6 (RX) GPIO7 (TX) GPIO5 (CTS) GPIO4 (RTS)
Despite the latter having a larger package, SDRAM footprints for 54-TFBGA 16Mx16 and 32Mx16 are interchangable and just require setting the FMC column address bits to 8 or 9 respectively on the firmware driver side. The footprint used here is interchangable for both, allowing selecting either 256Mb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
ESP32-C6 uses UART0 on 16/17 for programming.
Pull-down holds display in reset until the MCU is ready to initialize the display.
For download mode: GPIO8=1 GPIO9=0
https://www.buydisplay.com/3-5-inch-ips-tft-display-optl-capacitive-touch-lq035nc111-lq035nc211 https://www.buydisplay.com/ips-3-5-inch-full-viewing-640x480-tft-display-capacitive-touch-screen
Selects 256Mb or 512Mb
https://docs.espressif.com/projects/esp-at/en/latest/esp32c6/Get_Started/Downloading_guide.html
Input Board
